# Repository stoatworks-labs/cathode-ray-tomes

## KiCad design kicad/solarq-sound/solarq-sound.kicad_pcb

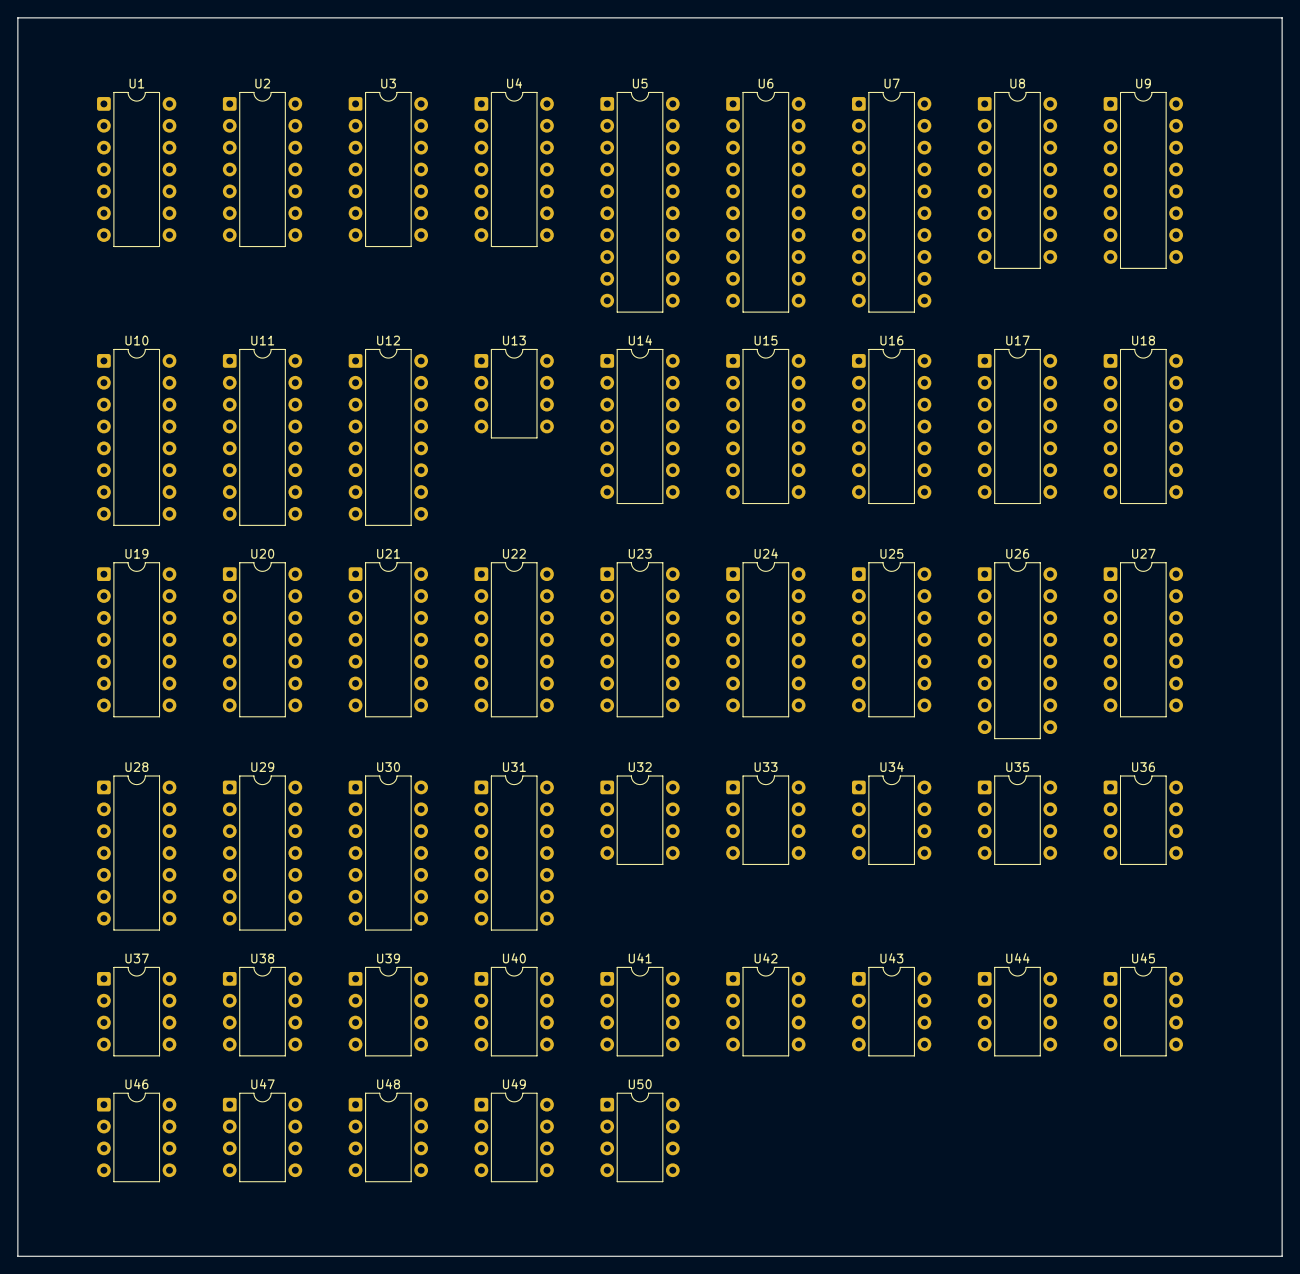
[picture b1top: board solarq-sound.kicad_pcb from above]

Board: 2 copper layers, 146.9 x 143.9 mm, 50 parts (0 on the bottom side), 107 nets, no tracks yet.

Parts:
U1, U2: 7414; DIP-14_W7.62mm
U3, U4, U28, U29, U30: 74LS164; DIP-14_W7.62mm
U5, U6, U7: 74LS377; DIP-20_W7.62mm
U8, U9, U10, U11, U12, U26: 74LS163; DIP-16_W7.62mm
U13, U35: LM555; DIP-8_W7.62mm
U14, U15, U19, U20, U23: 74LS74; DIP-14_W7.62mm
U16, U27: 74LS107; DIP-14_W7.62mm
U17, U21, U31: 74LS393; DIP-14_W7.62mm
U18: 74LS86; DIP-14_W7.62mm
U22: 74LS02; DIP-14_W7.62mm
U24: 74S04; DIP-14_W7.62mm
U25: 74S113A; DIP-14_W7.62mm
U32, U36, U37, U38, U39, U40, U43, U45, U47, U49, U50: TL081; DIP-8_W7.62mm
U33, U34, U41, U48: CA3080; DIP-8_W7.62mm
U42: LM566; DIP-8_W7.62mm
U44, U46: CA3080A; DIP-8_W7.62mm

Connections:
+5V: U1.14, U2.14, U3.14, U4.14, U5.20, U6.20, U7.20, U8.16, U9.16, U10.16, U11.16, U12.16, U13.8, U14.14, U15.14, U16.14, U17.14, U18.14, U19.14, U20.14, U21.14, U22.14, U23.14, U24.14, U25.14, U26.16, U27.14, U28.14, U29.14, U30.14, U31.14, U35.4, U35.8
+15V: U32.7, U33.7, U34.7, U36.7, U37.7, U38.7, U39.7, U40.7, U41.7, U42.8, U43.7, U44.7, U45.7, U46.7, U47.7, U48.7, U49.7, U50.7
-15V: U32.4, U33.4, U34.4, U36.4, U37.4, U38.4, U39.4, U40.4, U41.4, U43.4, U44.4, U45.4, U46.4, U47.4, U48.4, U49.4, U50.4
CAPTURE_M: U7.12, U21.2
CS: U33.6, U34.6, U41.6, U48.6, U49.3
FS00_P: U6.19, U10.3
FS01_P: U6.16, U10.4
FS02_P: U6.15, U10.5
FS03_P: U6.12, U10.6
FS04_P: U6.9, U9.3
FS05_P: U6.6, U9.4
FS06_P: U6.5, U9.5
FS07_P: U6.2, U9.6
FS08_P: U5.19, U8.3
FS09_P: U5.16, U8.4
FS10_P: U5.15, U8.5
FS11_P: U5.12, U8.6
GND: U1.7, U2.7, U3.7, U4.7, U5.1, U5.10, U6.1, U6.10, U7.1, U7.10, U8.8, U9.8, U10.8, U11.3, U11.4, U11.6, U11.8, U12.4, U12.5, U12.6, U12.8, U13.1, U14.7, U15.7, U16.7, U17.2, U17.7, U17.12, U18.7, U19.7, U20.7, U21.7, U22.7, U23.7, U24.7, U25.7, U26.4, U26.6, U26.8, U27.7, U28.7, U29.7, U30.7, U31.7, U35.1, U37.3, U40.2, U42.1, U43.3, U50.3
HIA_P: U3.2, U3.9, U4.2, U4.9, U16.8, U16.10, U16.11, U19.1, U19.4, U19.10, U19.13, U20.2, U20.4, U20.10, U23.4, U23.13
HIB_P: U8.1, U9.1, U10.1, U11.1, U11.5, U11.7, U12.1, U12.3, U12.7, U12.10, U14.1, U14.4, U14.10, U14.13, U15.10, U16.1, U16.4, U16.13
HIC_P: U15.4, U25.2, U25.3, U25.4, U25.10, U25.11, U25.12, U26.1, U26.3, U26.5, U26.7, U26.10, U27.1, U27.4, U27.13
IN_M: U24.8, U29.1, U29.2
KILL_FLAG_M: U20.1, U23.6
LATCH_CLK_P: U2.6, U20.3
MACLK_M: U19.2, U19.8, U20.11, U31.1
MACLK_P: U9.2, U19.9, U23.3, U28.8, U29.8, U30.8
MBCLK_M: U10.2, U19.6, U21.13
MBCLK_P: U8.2, U19.5, U19.12, U23.11
MCARRY_P: U8.15, U20.12
MEN_P: U5.2, U8.7, U9.7, U10.7, U10.10
MLATCH_P: U5.11, U6.11, U23.2, U23.9
MLOAD_M: U8.9, U9.9, U10.9, U20.8
NACLK_M: U12.2, U14.6
NBCLK_M: U14.2, U14.8, U15.11
NBCLK_P: U11.2, U14.9, U17.1
NLOAD_M: U11.9, U12.9, U15.8
NUKE_P: U7.15, U13.4
unnamed: U13.2, U13.6
unnamed: U24.2, U24.13
unnamed: U18.10, U30.13
unnamed: U35.2, U35.6
unnamed: U38.2, U39.2
unnamed: U44.6, U45.3
unnamed: U46.6, U47.3
unnamed: U49.2, U49.6
unnamed: U2.1, U13.3
unnamed: U47.2, U47.6
unnamed: U45.2, U45.6
unnamed: U1.2, U1.3
unnamed: U1.4, U3.1
unnamed: U1.8, U7.11
unnamed: U1.9, U1.10
unnamed: U1.12, U3.8, U4.8
unnamed: U1.6, U1.13
unnamed: U2.4, U2.5
unnamed: U3.3, U5.3, U7.3
unnamed: U3.4, U5.4, U7.4
unnamed: U3.5, U5.7, U7.7
unnamed: U3.6, U5.8, U7.8
unnamed: U3.10, U5.13, U7.13
unnamed: U3.11, U5.14, U7.14
unnamed: U3.12, U5.17, U7.17
unnamed: U3.13, U4.1, U5.18, U7.18
unnamed: U4.3, U6.3
unnamed: U4.4, U6.4
unnamed: U4.5, U6.7
unnamed: U4.6, U6.8
unnamed: U4.10, U6.13
unnamed: U4.11, U6.14
unnamed: U4.12, U6.17
unnamed: U4.13, U6.18
unnamed: U8.10, U9.15
unnamed: U9.10, U10.15
unnamed: U11.10, U12.15
unnamed: U11.15, U15.12
unnamed: U2.2, U2.13, U14.3
unnamed: U2.12, U14.11
unnamed: U14.5, U14.12
unnamed: U15.2, U26.15
unnamed: U15.6, U26.9, U27.12
unnamed: U15.9, U16.12
unnamed: U16.3, U18.2
unnamed: U16.9, U20.9, U22.8
unnamed: U17.9, U18.1
unnamed: U17.6, U17.13
unnamed: U18.4, U30.5
unnamed: U18.5, U30.6
unnamed: U18.9, U30.3
unnamed: U18.11, U24.9, U31.2, U31.12
unnamed: U18.6, U18.12
unnamed: U18.8, U18.13
unnamed: U20.6, U21.12, U22.9
unnamed: U21.9, U22.11, U22.12
unnamed: U22.10, U23.12
unnamed: U22.13, U23.10
unnamed: U24.11, U31.10
unnamed: U24.12, U25.1
unnamed: U25.5, U25.13
unnamed: U28.1, U28.2, U29.13
unnamed: U28.13, U30.1, U30.2
unnamed: U31.6, U31.13
RN_M: U24.10, U28.9, U29.9, U30.9
VP: U36.2, U36.6
_5MC_M: U15.3, U25.8
_5MC_P: U25.9, U26.2
_227KC_M: U19.11, U27.2
_227KC_P: U19.3, U27.3

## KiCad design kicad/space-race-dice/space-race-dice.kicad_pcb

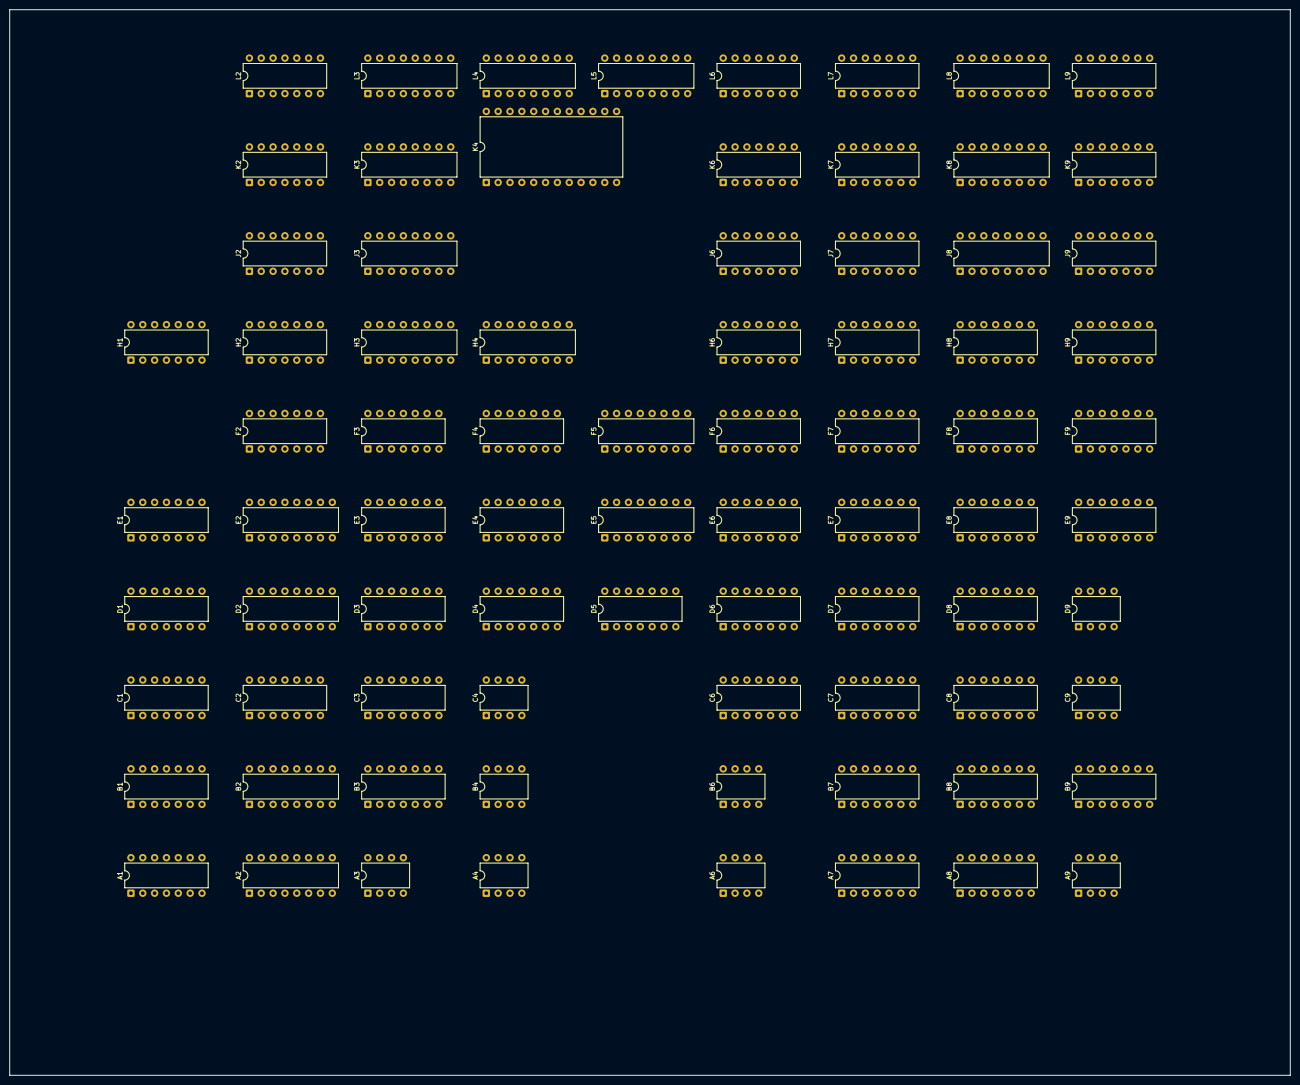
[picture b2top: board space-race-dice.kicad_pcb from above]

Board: 2 copper layers, 274.6 x 228.5 mm, 79 parts (0 on the bottom side), 211 nets, no tracks yet.

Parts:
A1: 7402; DIP-14_W7.62mm
A2: 9316; DIP-16_W7.62mm
A3, A6, A9: 555; DIP-8_W7.62mm
A4: 566; DIP-8_W7.62mm
A7: 7400; DIP-14_W7.62mm
A8: 7474; DIP-14_W7.62mm
B1: 7400; DIP-14_W7.62mm
B2: 9316; DIP-16_W7.62mm
B3, B8: 7474; DIP-14_W7.62mm
B4: 566; DIP-8_W7.62mm
B6: 555; DIP-8_W7.62mm
B7: 7402; DIP-14_W7.62mm
B9: 7404; DIP-14_W7.62mm
C1: 7427; DIP-14_W7.62mm
C2: 74107; DIP-14_W7.62mm
C3: 7493; DIP-14_W7.62mm
C4: 566; DIP-8_W7.62mm
C6: 7420; DIP-14_W7.62mm
C7: 7474; DIP-14_W7.62mm
C8: 7410; DIP-14_W7.62mm
C9: 555; DIP-8_W7.62mm
D1: 7493; DIP-14_W7.62mm
D2: 9316; DIP-16_W7.62mm
D3, D4, D6, D8: 7400; DIP-14_W7.62mm
D5, D7: 7404; DIP-14_W7.62mm
D9: 555; DIP-8_W7.62mm
E1: 7474; DIP-14_W7.62mm
E2, E5: 9316; DIP-16_W7.62mm
E3, E9: 7404; DIP-14_W7.62mm
E4: 7402; DIP-14_W7.62mm
E6, E8: 7410; DIP-14_W7.62mm
E7: 7427; DIP-14_W7.62mm
F2: 7400; DIP-14_W7.62mm
F3: 7402; DIP-14_W7.62mm
F4: 74107; DIP-14_W7.62mm
F5: 9316; DIP-16_W7.62mm
F6: 7493; DIP-14_W7.62mm
F7: 7474; DIP-14_W7.62mm
F8: 7410; DIP-14_W7.62mm
F9: 7430; DIP-14_W7.62mm
H1, H8: 7410; DIP-14_W7.62mm
H2: 7474; DIP-14_W7.62mm
H3: 9316; DIP-16_W7.62mm
H4: 9322; DIP-16_W7.62mm
H6: 7493; DIP-14_W7.62mm
H7: 74107; DIP-14_W7.62mm
H9: 7490; DIP-14_W7.62mm
J2: 7400; DIP-14_W7.62mm
J3: 9316; DIP-16_W7.62mm
J6: 7427; DIP-14_W7.62mm
J7: 7430; DIP-14_W7.62mm
J8: 7448; DIP-16_W7.62mm
J9: 7490; DIP-14_W7.62mm
K2: 7474; DIP-14_W7.62mm
K3: 9316; DIP-16_W7.62mm
K4: 9311; DIP-24_W15.24mm
K6: 7410; DIP-14_W7.62mm
K7: 7493; DIP-14_W7.62mm
K8: 74153; DIP-16_W7.62mm
K9: 7490; DIP-14_W7.62mm
L2: 7400; DIP-14_W7.62mm
L3: 9316; DIP-16_W7.62mm
L4: 9602; DIP-16_W7.62mm
L5: 9312; DIP-16_W7.62mm
L6: 7486; DIP-14_W7.62mm
L7: 7493; DIP-14_W7.62mm
L8: 74153; DIP-16_W7.62mm
L9: 7490; DIP-14_W7.62mm

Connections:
+5V: A1.14, A2.16, A3.8, A6.8, A7.14, A8.14, A9.8, B1.14, B2.16, B3.14, B6.8, B7.14, B8.14, B9.14, C1.14, C2.14, C3.5, C6.14, C7.14, C8.14, C9.8, D1.5, D2.16, D3.14, D4.14, D5.14, D6.14, D7.14, D8.14, D9.8, E1.14, E2.16, E3.14, E4.14, E5.16, E6.14, E7.14, E8.14, E9.14, F2.14, F3.14, F4.14, F5.16, F6.5, F7.14, F8.14, F9.14, H1.14, H2.14, H3.16, H4.16, H6.5, H7.14, H8.14, H9.5, J2.14, J3.16, J6.14, J7.14, J8.16, J9.5, K2.14, K3.16, K4.24, K6.14, K7.5, K8.16, K9.5, L2.14, L3.16, L5.16, L6.14, L7.5, L8.16, L9.5
A1-1: A1.1, A3.2
A1-2: A1.2, A1.3, A1.13, D3.4, D3.10
A1-4: A1.4, D5.5, E4.6, E5.9, F5.9, H1.13
A1-5: A1.5, C1.12
A1-6: A1.6, C1.8
A1-10: A1.10, C1.1, C1.11, D1.14, E1.11, F4.12
A2-9: A2.9, B1.6, B2.9, C1.9
A2-15: A2.15, B2.10
A3-3: A3.3, D5.13
A6-2: A6.2, D3.8
A6-3: A6.3, D5.9
A7-2: A7.2, D7.10
A7-3: A7.3, B8.2
A7-6: A7.6, A7.9
A8-1: A8.1, B8.8
A8-2: A8.2, A8.9
A8-3: A8.3, A8.11, B9.2, C8.11, D8.12
A8-5: A8.5, D8.13
A8-6: A8.6, C8.9
A9-3: A9.3, B9.9
B1-1: B1.1, C2.12, D2.15
B1-2: B1.2, C2.3
B1-3: B1.3, C1.13, D2.9, E2.9
B1-4: B1.4, C2.5
B1-5: B1.5, B2.15, C2.9
B1-8: B1.8, F3.11
B1-10: B1.10, K2.6
B1-11: B1.11, D1.2, D1.3
B1-12: B1.12, C1.2, E1.8
B3-3: B3.3, C6.12, H2.2, H2.12, H3.15, J2.9
B3-11: B3.11, C6.2, K2.2, K2.12, K3.15, L2.10
B6-2: B6.2, D3.6
B6-3: B6.3, D5.11
B7-8: B7.8, D6.11
B7-9: B7.9, D7.2, E7.3, E7.13
B7-10: B7.10, F8.4, H8.3
B7-13: B7.13, B8.1
B8-11: B8.11, B9.8
B8-12: B8.12, B8.13, B9.12
B9-6: B9.6, C8.10
C1-3: C1.3, D1.1, D1.12
C1-4: C1.4, E3.10
C1-5: C1.5, D1.9
C1-6: C1.6, E3.9, F4.4
C1-10: C1.10, F4.3
C3-1: C3.1, C3.12
C3-8: C3.8, D4.12
C3-11: C3.11, F2.13
C6-5: C6.5, J6.6
C6-6: C6.6, D6.9
C6-8: C6.8, D6.10
C6-9: C6.9, J6.12
C7-2: C7.2, L5.14
C8-1: C8.1, D7.12
C8-4: C8.4, E9.2
C8-5: C8.5, L4.6
C8-6: C8.6, D8.1
C8-8: C8.8, C9.2, E9.3
CLK: A2.2, B2.2, C7.8, C7.12, D2.2, E2.2, E4.11, E4.12, F7.3, L7.14
CLK_n: C7.3, C7.9
CRASH1_n: C6.10, D5.8, J2.5
CRASH2_n: C6.4, D5.10, L2.5
D1-8: D1.8, E3.11
D1-11: D1.11, E1.12
D2-10: D2.10, E2.15
D3-13: D3.13, H2.6
D4-2: D4.2, D4.5, D5.6
D4-3: D4.3, D4.4, F4.11
D4-6: D4.6, F4.8
D4-8: D4.8, L4.11
D4-9: D4.9, E5.15, F3.2, F3.3, H1.1
D4-10: D4.10, F4.5, H1.2
D4-13: D4.13, D5.2
D5-1: D5.1, J2.6, J2.12
D6-2: D6.2, D6.6, E6.9
D6-3: D6.3, D6.4, E5.1, F4.10, F5.1
D6-5: D6.5, E3.13, K6.6
D7-4: D7.4, E7.9, E8.11
D7-5: D7.5, E7.8
D7-6: D7.6, D8.5
D7-8: D7.8, F8.11, F8.13
D7-9: D7.9, E6.12
D8-2: D8.2, E8.12
D8-4: D8.4, E8.8
D8-6: D8.6, E8.13
D9-3: D9.3, E9.1
E1-2: E1.2, E6.8, F3.5
E1-6: E1.6, F3.6, H2.3, K2.3
E3-1: E3.1, L2.6, L2.12
E3-2: E3.2, F2.12
E3-3: E3.3, F3.13
E3-4: E3.4, L2.2, L3.4
E3-5: E3.5, F3.10
E3-6: E3.6, J2.2, J3.4
E3-8: E3.8, F4.1
E4-1: E4.1, F4.9
E4-2: E4.2, F3.1
E4-3: E4.3, E4.4
E4-5: E4.5, E5.2, F5.2, H1.8
E4-13: E4.13, H1.9, H1.10
E5-10: E5.10, F5.15
E6-6: E6.6, F7.12
E7-6: E7.6, H8.10, H8.13
E7-12: E7.12, E8.3
E8-1: E8.1, F9.8
E8-4: E8.4, E9.6, F8.1, F8.3, H8.1
E8-5: E8.5, J8.13
E8-6: E8.6, F9.11
E9-4: E9.4, H9.2, H9.3, J9.2, J9.3, K9.2, K9.3, L9.2, L9.3
F7-2: F7.2, J7.8
F8-2: F8.2, J8.14
F8-5: F8.5, J8.12
F8-6: F8.6, F9.5
F8-8: F8.8, F9.6
F8-9: F8.9, J8.10
F8-12: F8.12, F9.12
F9-2: F9.2, H8.6
F9-3: F9.3, H8.8
F9-4: F9.4, H8.12
GAME_ON: B9.1, C8.3, C9.3, D9.5, J2.4, L2.4
GND: A1.7, A2.5, A2.8, A3.1, A6.1, A7.7, A8.7, A9.1, B1.7, B2.5, B2.6, B2.8, B3.7, B6.1, B7.7, B8.7, B9.7, C1.7, C2.7, C3.2, C3.3, C3.10, C6.7, C7.7, C8.7, C9.1, D1.10, D2.5, D2.6, D2.8, D3.7, D4.7, D5.7, D6.7, D7.7, D8.7, D9.1, E1.7, E2.4, E2.5, E2.8, E3.7, E4.7, E5.8, E6.7, E7.7, E8.7, E9.7, F2.7, F3.7, F4.7, F5.3, F5.8, F6.10, F7.7, F8.7, F9.7, H1.7, H2.7, H3.3, H3.4, H3.5, H3.6, H3.8, H4.8, H4.15, H6.10, H7.7, H8.7, H9.6, H9.7, H9.10, J2.7, J3.5, J3.8, J6.7, J7.7, J8.8, J9.6, J9.7, J9.10, K2.7, K3.3, K3.4, K3.5, K3.6, K3.8, K4.12, K4.18, K4.19, K6.7, K7.10, K8.1, K8.8, K8.15, K9.6, K9.7, K9.10, L2.7, L3.5, L3.8, L4.4, L4.12, L5.8, L5.10, L6.7, L7.10, L8.1, L8.8, L8.15, L9.6, L9.7, L9.10
H1: L6.4, L7.1, L7.12
H1-11: H1.11, H1.12
H2: J7.3, L6.10, L7.9
H3-1: H3.1, J2.11, J3.1
H3-7: H3.7, J2.10, J3.15
H3-9: H3.9, J2.8, J3.9
H4: D6.13, E7.4, J7.5, L6.13, L7.8
H4-4: H4.4, K4.23
H4-7: H4.7, K4.22
H4-9: H4.9, K4.20
H4-12: H4.12, K4.21
H8: D6.12, E7.5, K7.14, L6.5, L6.9, L6.12, L7.11
H8-2: H8.2, J8.15
H8-5: H8.5, J8.11
H8-9: H8.9, J8.9
H9-1: H9.1, H9.12, L8.6
H9-8: H9.8, K8.6
H9-9: H9.9, L8.10
H9-11: H9.11, K8.10
H9-14: H9.14, J9.11, K8.11
H16: A7.5, B8.3, D7.1, E6.13, J6.2, K6.2, K7.1, K7.12
H32: A7.1, J6.1, J8.5, K6.1, K7.9, K8.14, L8.14
H64: A7.4, B7.11, D7.3, D7.11, J6.4, J7.6, K6.11, K7.8, K8.2, L8.2
H128: E7.10, E8.10, H7.9, J6.5, J7.4, K6.10, K7.11
H256: D3.5, H4.1, H7.5, J7.11, K6.13
H256_n: D3.9, E7.11, E8.9, H7.6, K6.9, L4.5
HBLANK: A7.10, A7.11
HBLANK_n: A7.8, A7.12, B7.12
HRESET: F6.14, F7.6, F7.11, K7.2, K7.3, L7.2, L7.3
HRESET_n: A1.8, A1.9, A7.13, F7.5, H7.10
HSYNC: B8.5, E1.3
HSYNC_n: B8.6, H3.2, J3.2, K3.2, L3.2
J2-3: J2.3, J3.3
J6-3: J6.3, K6.12
J6-13: J6.13, K6.8
J8-1: J8.1, L8.9
J8-2: J8.2, K8.7
J8-6: J8.6, K8.9
J8-7: J8.7, L8.7
J9-1: J9.1, J9.12, L8.5
J9-8: J9.8, K8.5
J9-9: J9.9, L8.11
K3-1: K3.1, L2.11, L3.1
K3-7: K3.7, L2.9, L3.15
K3-9: K3.9, L2.8, L3.9
K8-3: K8.3, L9.8
K8-4: K8.4, K9.8
K8-12: K8.12, K9.11
K8-13: K8.13, K9.14, L9.11
K9-1: K9.1, K9.12, L8.4
K9-9: K9.9, L8.12
L2-3: L2.3, L3.3
L5-11: L5.11, L6.6
L5-12: L5.12, L6.8
L5-13: L5.13, L6.11
L8-3: L8.3, L9.1, L9.12
L8-13: L8.13, L9.9
QA1: H4.2, J3.14
QA2: H4.3, L3.14
QB1: H4.5, J3.13
QB2: H4.6, L3.13
QC1: H4.14, J3.12
QC2: H4.13, L3.12
QD1: H4.11, J3.11
QD2: H4.10, L3.11
RESET_n: B9.13, C2.13, D2.1, E2.1, F7.1, F7.13
ROCKETS_n: A1.12, C7.6, D3.1
ROCKET_WINDOW: C7.1, D6.8
RRESET: F3.4, J2.13, L2.13
SCORE1: D3.12, H2.8, J9.14
SCORE2: B1.9, K2.8, L9.14
STARS_n: A1.11, D3.2, L4.9
STAR_BLANK: E3.12, E8.2
STOP1: D3.11, F3.8
V1: D4.1, E6.5, F6.1, F6.12
V2: E5.6, F6.9
V4: C8.13, E5.5, E6.1, E6.4, E7.2, F6.8
V8: D7.13, E5.4, E6.2, E6.11, E7.1, F6.11, H6.14
V16: B7.2, E5.3, E6.10, E9.5, F8.10, H6.1, H6.12, H8.4, H8.11
V32: F5.6, H6.9, K6.4
V64: F5.5, H6.8, K6.5
V128: F5.4, H6.11, H7.12, K6.3
V256: E6.3, H7.3
V256_n: D9.2, H7.2
VBLANK: B7.1, B7.5, C8.2, H2.11
VBLANK_n: B1.13, B7.3, B7.4, J3.10, K2.11, L3.10, L4.3
VCC: A2.1, A2.6, A2.7, A2.10, A3.4, A6.4, A8.4, A8.12, A9.4, B2.1, B2.3, B2.4, B2.7, B3.2, B3.4, B3.10, B3.12, B6.4, B8.4, B8.10, C2.1, C2.4, C2.8, C2.10, C2.11, C7.4, C7.10, C7.13, D2.3, D2.4, D2.7, E1.1, E1.4, E1.10, E1.13, E2.6, E2.7, E2.10, E5.7, F4.13, F5.7, F5.10, F7.4, F7.10, F9.1, H2.1, H2.4, H2.10, H2.13, H3.10, H7.1, H7.4, H7.8, H7.11, J3.6, J3.7, J7.1, J7.2, J7.12, J8.3, J8.4, K2.1, K2.4, K2.10, K2.13, K3.10, L3.6, L3.7, L4.13
VRESET: A2.4, B7.6, F6.2, F6.3, F7.8, H6.2, H6.3
VRESET_n: A2.3, B3.1, B3.13, C3.14, C6.1, C6.13, D6.1, E2.3, F7.9, H7.13

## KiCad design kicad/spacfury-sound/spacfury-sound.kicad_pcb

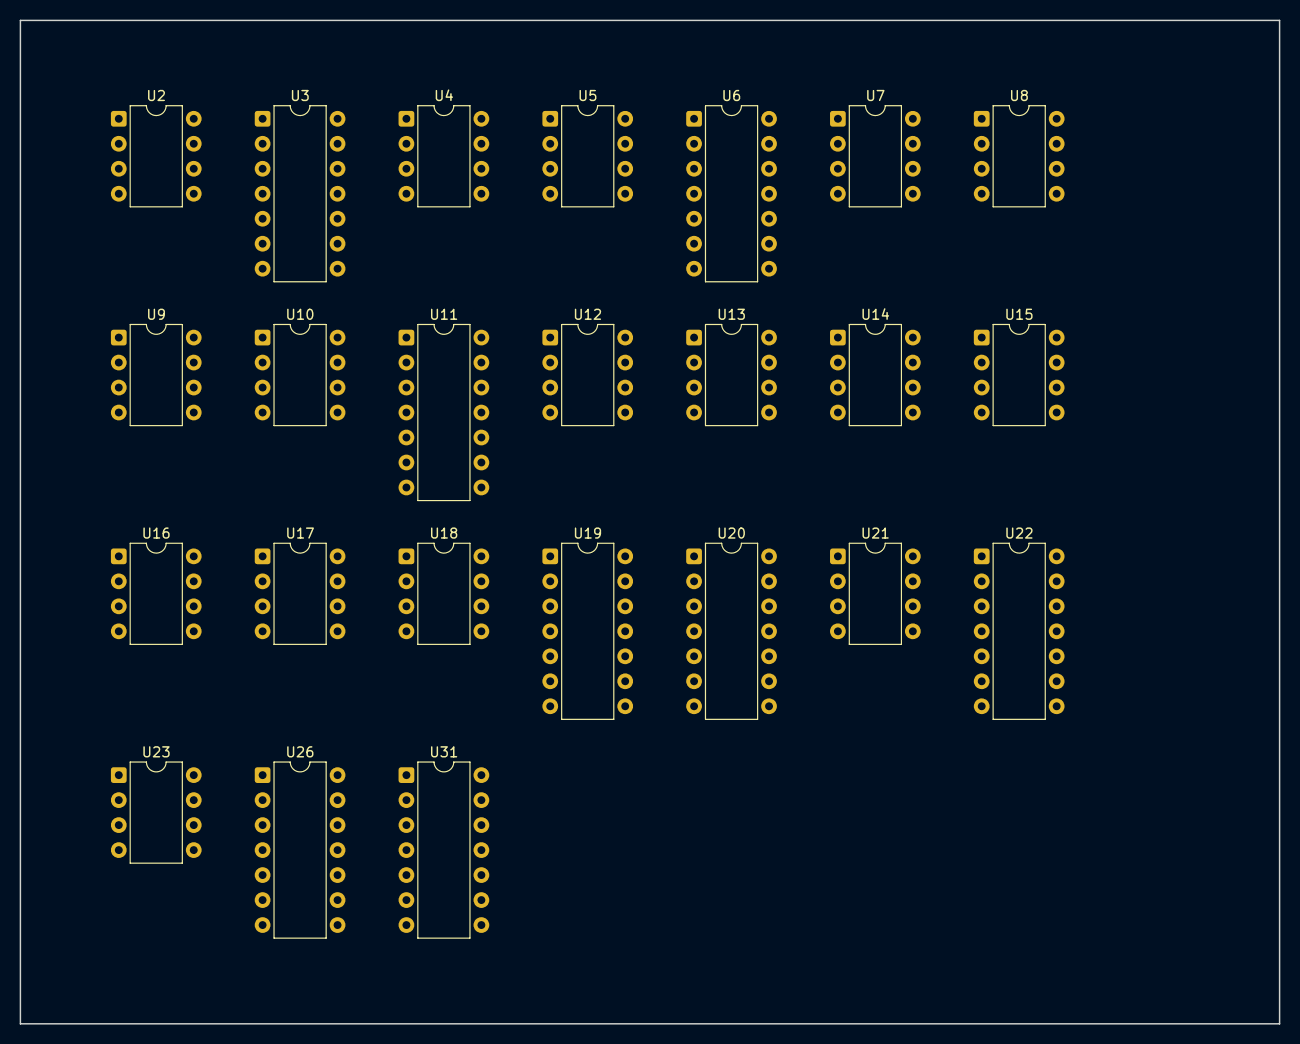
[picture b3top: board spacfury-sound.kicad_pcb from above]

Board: 2 copper layers, 128.0 x 102.0 mm, 24 parts (0 on the bottom side), 28 nets, no tracks yet.

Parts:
U2, U4, U5, U8, U10, U13, U14, U15, U16, U18, U21, U23: TL082; DIP-8_W7.62mm
U3, U19: CD4069; DIP-14_W7.62mm
U6, U20, U22: CD4011; DIP-14_W7.62mm
U7, U12: CA3080; DIP-8_W7.62mm
U9: MM5837; DIP-8_W7.62mm
U11: CD4024; DIP-14_W7.62mm
U17: LM555; DIP-8_W7.62mm
U26: 7407; DIP-14_W7.62mm
U31: 7406; DIP-14_W7.62mm

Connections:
+5V: U26.14, U31.14
+12V: U2.8, U3.14, U4.8, U5.8, U6.14, U7.7, U8.8, U9.4, U10.8, U11.14, U12.7, U13.8, U14.8, U15.8, U16.8, U17.8, U18.8, U19.14, U20.14, U21.8, U22.14, U23.8
-12V: U2.4, U4.4, U5.4, U7.4, U8.4, U9.2, U10.4, U12.4, U13.4, U14.4, U15.4, U16.4, U18.4, U21.4, U23.4
GND: U3.7, U4.3, U4.5, U6.7, U7.2, U8.3, U9.1, U10.3, U11.7, U12.2, U13.3, U17.1, U18.5, U19.7, U20.7, U22.7, U23.3, U26.7, U31.7
I_STAR_SPIN: U31.1, U31.3
unnamed: U2.1, U2.2
unnamed: U5.1, U5.2
unnamed: U7.6, U8.2
unnamed: U14.1, U14.2
unnamed: U12.6, U13.2
unnamed: U15.6, U15.7
unnamed: U16.2, U16.7
unnamed: U17.2, U17.6
unnamed: U11.2, U22.4
unnamed: U6.3, U6.5, U6.6
unnamed: U6.8, U6.9, U6.11
unnamed: U13.6, U13.7
unnamed: U22.3, U22.5, U22.6
unnamed: U6.2, U26.12
unnamed: U6.12, U26.6
unnamed: U20.12, U26.2
unnamed: U20.2, U26.4
unnamed: U22.8, U22.9, U22.11
unnamed: U22.12, U26.10
unnamed: U22.2, U26.8
unnamed: U17.4, U31.8
unnamed: U20.3, U20.5, U20.6
unnamed: U20.8, U20.9, U20.11

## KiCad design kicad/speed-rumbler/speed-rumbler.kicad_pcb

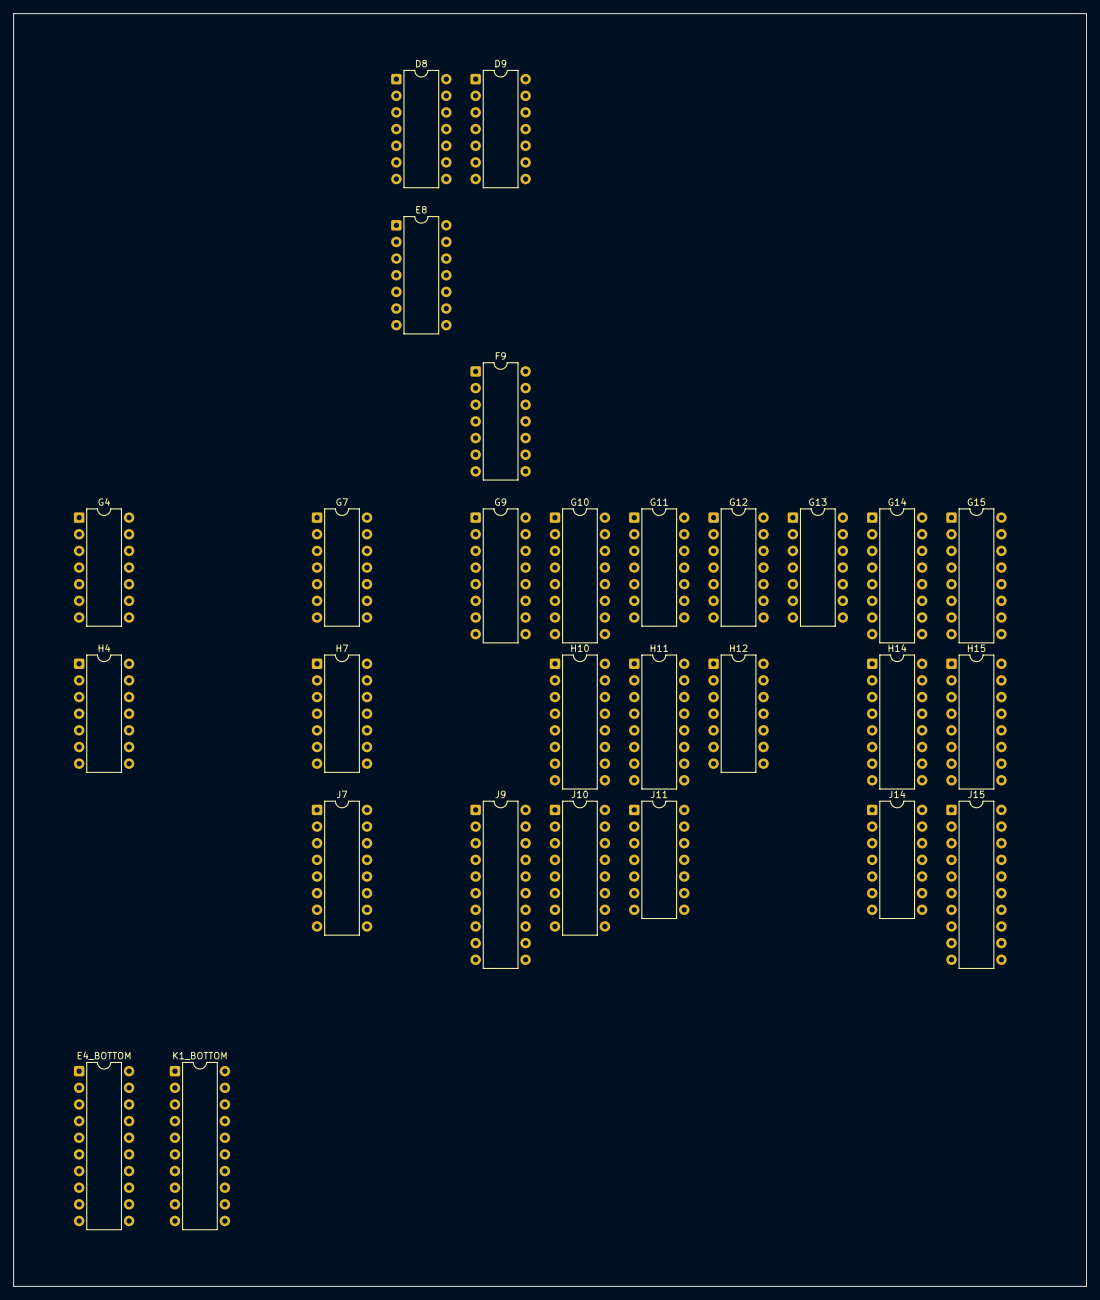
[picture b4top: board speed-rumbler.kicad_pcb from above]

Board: 2 copper layers, 163.7 x 194.2 mm, 28 parts (0 on the bottom side), 59 nets, no tracks yet.

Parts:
D8: 74LS86; DIP-14_W7.62mm
D9: 74LS32; DIP-14_W7.62mm
E4_BOTTOM: 74LS27; DIP-20_W7.62mm
E8: 74LS86; DIP-14_W7.62mm
F9: 74LS86; DIP-14_W7.62mm
G4, G13: 74LS04; DIP-14_W7.62mm
G7, G12: 74LS74; DIP-14_W7.62mm
G9: 74LS174; DIP-16_W7.62mm
G10: 74LS153; DIP-16_W7.62mm
G11: 74LS10; DIP-14_W7.62mm
G14, G15: 74LS161; DIP-16_W7.62mm
H4: 74LS86; DIP-14_W7.62mm
H7: 74LS00; DIP-14_W7.62mm
H10, H11: 74LS153; DIP-16_W7.62mm
H12: 74LS08; DIP-14_W7.62mm
H14, H15: 74LS161; DIP-16_W7.62mm
J7: 82S126-9; DIP-16_W7.62mm
J9: 74LS273; DIP-20_W7.62mm
J10: 74LS153; DIP-16_W7.62mm
J11, J14: 74LS74; DIP-14_W7.62mm
J15: 74LS245; DIP-20_W7.62mm
K1_BOTTOM: 74LS273; DIP-20_W7.62mm

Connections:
/CHARA: H7.1, J9.19, J10.13
/CHARB: H7.2, J9.16, J10.3
/CHARC: H10.13, J9.15
/CHARD: H10.3, J9.12
/CHARE: H11.13, J9.9
/CHARF: H11.3, J9.6
/CHARG: J7.6, J9.5
/CHARH: G9.3, J9.2
/OBJA: J10.12, K1_BOTTOM.19
/OBJB: J10.4, K1_BOTTOM.16
/OBJC: H10.12, K1_BOTTOM.15
/OBJD: H10.4, K1_BOTTOM.12
/OBJE: H11.12, K1_BOTTOM.9
/OBJF: H11.4, K1_BOTTOM.6
/OBJG: G10.12, K1_BOTTOM.5
/OBJH: J7.7, K1_BOTTOM.2
/SCRA: E4_BOTTOM.19, J7.4, J10.11
/SCRB: E4_BOTTOM.16, J7.3, J10.5
/SCRC: E4_BOTTOM.15, H10.11, J7.2
/SCRD: E4_BOTTOM.12, H10.5, J7.1
/SCRE: E4_BOTTOM.9, H11.11
/SCRF: E4_BOTTOM.6, H11.5
/SCRG: E4_BOTTOM.5, G10.11
/SCRH: E4_BOTTOM.2, J7.15
/VDD: G10.3, G10.4, G10.5, G10.13
/timing/H8: E8.9, G15.12
/timing/H16: D8.9, E8.4, G15.11
/timing/H32: E8.1, G12.3, H15.14
/timing/H64: F9.9, G11.13, H15.13
/timing/H128: G11.2, H15.12
/timing/H256: G11.1, G13.5, H15.11
/timing/V2: G14.14, H4.4
/timing/V4: G12.11, G14.13, H4.1
/timing/V8: D9.13, G14.12, J11.3
/timing/V16: G14.11, H12.10
/timing/V32: H12.9, H14.14
/timing/V64: D8.1, H14.13
/timing/V128: E8.12, H14.12
/timing/V256: D9.12, H14.11
/timing/VDD: G12.1, G12.4, G12.10, G12.13, G14.1, G14.6, G15.1, G15.9, H14.1, H14.3, H14.4, H14.5, H15.1, H15.9, J14.10, J14.13
/timing/VSS: G14.3, G14.4, G14.5, G15.3, G15.4, G15.5, G15.6, H14.6, H15.3, H15.4, H15.5, H15.6, J15.1, J15.19
/timing/XH2: G4.1, G15.14
/timing/XH4: G15.13, H4.13
unnamed: G7.12, H15.15
unnamed: G11.12, G12.2
unnamed: G12.5, H12.4
unnamed: D9.11, G12.12
unnamed: G12.9, H12.5
unnamed: G14.7, G14.10, J11.8, J11.12
unnamed: G13.6, G14.2, H14.2, J11.11
unnamed: G14.15, H14.7, H14.10
unnamed: G13.4, G14.9, H14.9
unnamed: G15.7, G15.10, J14.9
unnamed: G15.2, H15.2, J14.11, J15.6
unnamed: G15.15, H15.7, H15.10
unnamed: G13.3, H14.15
unnamed: H7.3, J7.5
unnamed: J14.8, J14.12
VSS: G10.1, G10.6, G10.10, G10.15, H10.1, H10.6, H10.10, H10.15, H11.1, H11.6, H11.10, H11.15, J7.8, J7.13, J7.14, J10.1, J10.6, J10.10, J10.15

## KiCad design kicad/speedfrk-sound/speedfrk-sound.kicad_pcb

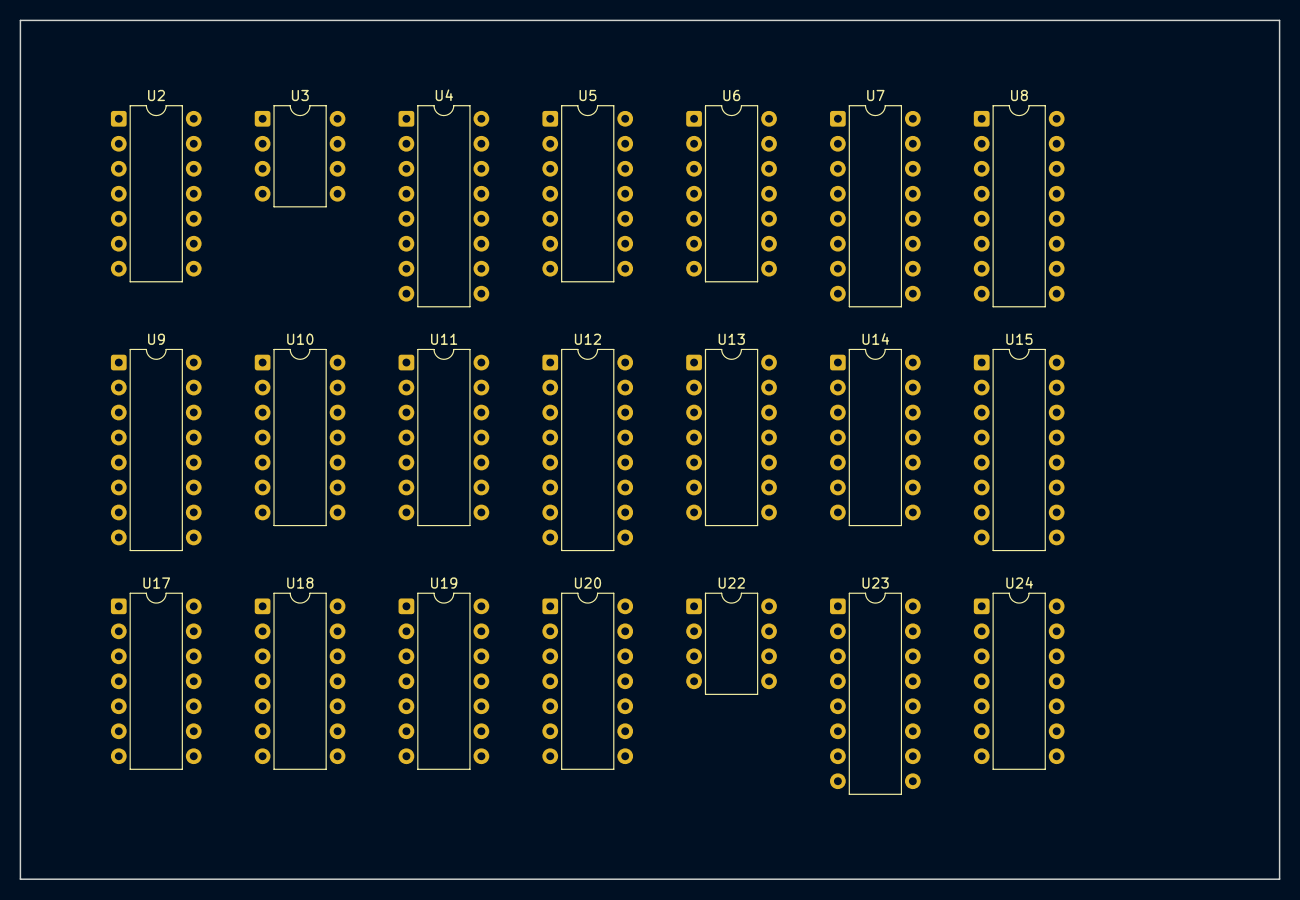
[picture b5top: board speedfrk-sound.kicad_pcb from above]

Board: 2 copper layers, 128.0 x 87.3 mm, 21 parts (0 on the bottom side), 68 nets, no tracks yet.

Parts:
U2, U10: 74LS04; DIP-14_W7.62mm
U3: TL081; DIP-8_W7.62mm
U4, U7, U8, U9, U15, U23: 74LS163; DIP-16_W7.62mm
U5, U17: 74LS107; DIP-14_W7.62mm
U6, U11: 74LS08; DIP-14_W7.62mm
U12: 74LS75; DIP-16_W7.62mm
U13, U14, U20, U24: 74LS164; DIP-14_W7.62mm
U18: 74LS393; DIP-14_W7.62mm
U19: 74LS86; DIP-14_W7.62mm
U22: LM555; DIP-8_W7.62mm

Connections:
+5V: U2.14, U3.7, U4.1, U4.3, U4.10, U4.16, U5.14, U6.14, U7.16, U8.16, U9.16, U10.14, U11.14, U12.5, U13.14, U14.14, U15.16, U17.14, U18.14, U19.14, U20.14, U22.4, U22.8, U23.16, U24.14
C2MHZ: U4.2, U5.9, U10.6
GND: U2.7, U3.4, U4.4, U4.5, U4.8, U5.4, U5.7, U6.7, U7.3, U7.4, U7.6, U7.8, U8.8, U9.8, U10.7, U11.7, U12.12, U13.7, U14.7, U15.8, U17.7, U18.2, U18.7, U18.12, U19.7, U20.7, U22.1, U23.4, U23.6, U23.8, U24.7
unnamed: U10.4, U10.5
unnamed: U22.2, U22.6
unnamed: U2.6, U6.5
unnamed: U7.1, U7.5
unnamed: U17.1, U17.4, U17.8, U17.11
unnamed: U4.6, U8.10
unnamed: U8.1, U8.7, U9.1, U9.7
unnamed: U13.9, U14.9
unnamed: U19.9, U19.12
unnamed: U23.1, U23.3, U23.5, U23.7, U23.10
unnamed: U15.1, U15.7, U20.9
unnamed: U11.2, U11.5, U11.9, U11.12, U24.13
unnamed: U2.2, U6.4
unnamed: U4.9, U5.6
unnamed: U5.3, U5.8
unnamed: U5.2, U5.11
unnamed: U8.15, U9.10
unnamed: U4.7, U10.8
unnamed: U4.15, U5.10, U5.13, U10.9
unnamed: U8.9, U9.9, U10.10, U15.9
unnamed: U7.10, U10.11, U15.15
unnamed: U7.9, U10.12
unnamed: U7.15, U10.13
unnamed: U11.1, U12.16
unnamed: U11.4, U12.15
unnamed: U11.10, U12.10
unnamed: U11.13, U12.9
unnamed: U12.2, U13.13
unnamed: U12.3, U13.12
unnamed: U12.6, U13.11
unnamed: U12.7, U13.10
unnamed: U2.5, U6.8, U6.12, U12.4, U12.13
unnamed: U9.3, U13.1, U13.2, U14.13
unnamed: U8.6, U13.3
unnamed: U8.5, U13.4
unnamed: U8.4, U13.5
unnamed: U8.3, U13.6
unnamed: U2.4, U13.8, U14.8
unnamed: U2.10, U14.1, U14.2
unnamed: U14.3, U15.6
unnamed: U14.4, U15.5
unnamed: U14.5, U15.4
unnamed: U14.6, U15.3
unnamed: U9.6, U14.10
unnamed: U9.5, U14.11
unnamed: U9.4, U14.12
unnamed: U6.11, U8.2, U9.2, U15.2
unnamed: U9.15, U15.10
unnamed: U17.9, U19.8, U23.9
unnamed: U2.8, U17.10, U17.13
unnamed: U17.12, U18.8
unnamed: U4.14, U6.13, U7.2, U18.1
unnamed: U18.10, U20.8, U24.8
unnamed: U18.11, U23.2
unnamed: U18.6, U18.13
unnamed: U19.1, U20.12
unnamed: U19.2, U24.12
unnamed: U19.3, U20.2
unnamed: U19.4, U20.13
unnamed: U19.6, U24.1, U24.2
unnamed: U19.10, U23.15
unnamed: U19.11, U20.1
unnamed: U6.6, U19.5, U19.13
unnamed: U6.1, U22.3
STEERING: U2.1, U2.12, U7.7

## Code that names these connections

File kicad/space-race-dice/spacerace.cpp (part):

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		Defines
	**************************************************************************/
	#define CLK "C7", 8
    #define CLK_n "C7", 9

	#define H1 "L7", 12
	#define H2 "L7", 9
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	#define H128 "K7", 11

	#define H256 "H7", 5
	#define H256_n "H7", 6

	#define HRESET "F7", 6
	#define HRESET_n "F7", 5

	#define V1 "F6", 12
	#define V2 "F6", 9
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	#define V128 "H6", 11

	#define V256 "H7", 3
	#define V256_n "H7", 2

	#define VRESET "F7", 8
	#define VRESET_n "F7", 9

	#define VBLANK "B7", 1
	#define VBLANK_n "B7", 4
	#define VSYNC_n "C8", 12

	#define HBLANK "A7", 11
	#define HBLANK_n "A7", 8
	#define HSYNC "B8", 5
	#define HSYNC_n "B8", 6

    #define RESET_n "COIN", 1
    #define GAME_ON "C9", 3
    #define CRASH1_n "D5", 8
    #define CRASH2_n "D5", 10

	#define STAR_BLANK "E3", 12

	#define ROCKET_WINDOW "D6", 8

	#define RRESET "F3", 4

	#define QA1 "J3", 14
	#define QB1 "J3", 13
	#define QC1 "J3", 12
	#define QD1 "J3", 11

	#define SCORE1 "H2", 8
	#define STOP1 "D3", 11

	#define QA2 "L3", 14
	#define QB2 "L3", 13
	#define QC2 "L3", 12
	#define QD2 "L3", 11

	#define SCORE2 "K2", 8

	#define STARS_n "L4", 9
	#define ROCKETS_n "C7", 6


	/**************************************************************************
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    CONNECTION("VIDEO", 1, "D3", 3)
    CONNECTION("VIDEO", 2, "D8", 3)

    CONNECTION("VIDEO", Video::HBLANK_PIN, HBLANK)
    CONNECTION("VIDEO", Video::VBLANK_PIN, VBLANK)



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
